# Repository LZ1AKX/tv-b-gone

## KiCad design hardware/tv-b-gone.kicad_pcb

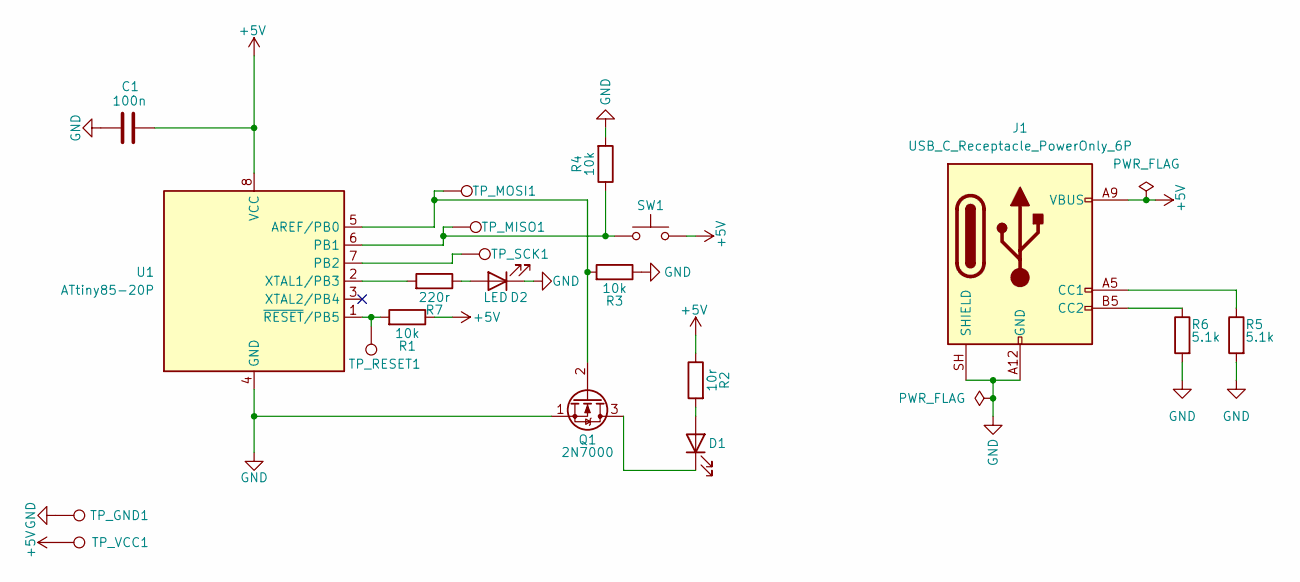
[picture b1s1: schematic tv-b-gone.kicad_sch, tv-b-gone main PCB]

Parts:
C1: 100n; C_0805_2012Metric
D1: LED; LED_D5.0mm
D2: LED; LED_D3.0mm
J1: USB_C_Receptacle_PowerOnly_6P; USB_C_Receptacle_GCT_USB4125-xx-x-0190_6P_TopMnt_Horizontal
Q1: 2N7000; TO-92_Inline
R1, R3, R4: 10k; R_0805_2012Metric
R2: 10r; R_0805_2012Metric
R5, R6: 5.1k; R_0805_2012Metric
R7: 220r; R_0805_2012Metric
SW1: SW_Push; SW_PUSH_6mm
TP_GND1: TestPoint; TestPoint_Pad_D2.0mm
TP_MISO1: TestPoint; TestPoint_Pad_D2.0mm
TP_MOSI1: TestPoint; TestPoint_Pad_D2.0mm
TP_RESET1: TestPoint; TestPoint_Pad_D2.0mm
TP_SCK1: TestPoint; TestPoint_Pad_D2.0mm
TP_VCC1: TestPoint; TestPoint_Pad_D2.0mm
U1: ATtiny85-20P; DIP-8_W7.62mm

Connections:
+5V: C1.2, J1.A9 (VBUS), J1.B9 (VBUS), R1.1, R2.1, SW1.2, TP_VCC1.1 (1_1), U1.8 (VCC)
GND: C1.1, D2.1 (K), J1.A12 (GND), J1.B12 (GND), J1.SH (SHIELD), Q1.1 (S), R3.1, R4.2, R5.2, R6.2, TP_GND1.1 (1_1), U1.4 (GND)
unnamed: D1.2 (A), R2.2
unnamed: D1.1 (K), Q1.3 (D)
unnamed: D2.2 (A), R7.1
unnamed: J1.A5 (CC1), R5.1
unnamed: J1.B5 (CC2), R6.1
unnamed: Q1.2 (G), R3.2, TP_MOSI1.1 (1_1), U1.5 (AREF/PB0)
unnamed: R4.1, SW1.1, TP_MISO1.1 (1_1), U1.6 (PB1)
unnamed: TP_SCK1.1 (1_1), U1.7 (PB2)
unnamed: R7.2, U1.2 (XTAL1/PB3)
unnamed: R1.2, TP_RESET1.1 (1_1), U1.1 (~RESET/PB5)

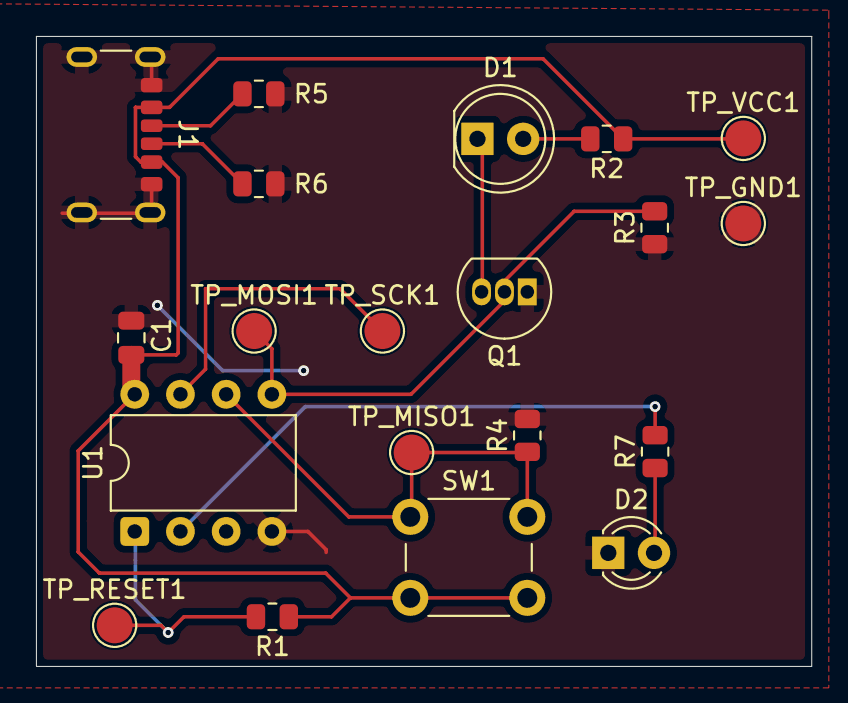
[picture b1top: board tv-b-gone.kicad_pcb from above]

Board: 2 copper layers, 43.1 x 35.0 mm, 20 parts (0 on the bottom side), 12 nets.
